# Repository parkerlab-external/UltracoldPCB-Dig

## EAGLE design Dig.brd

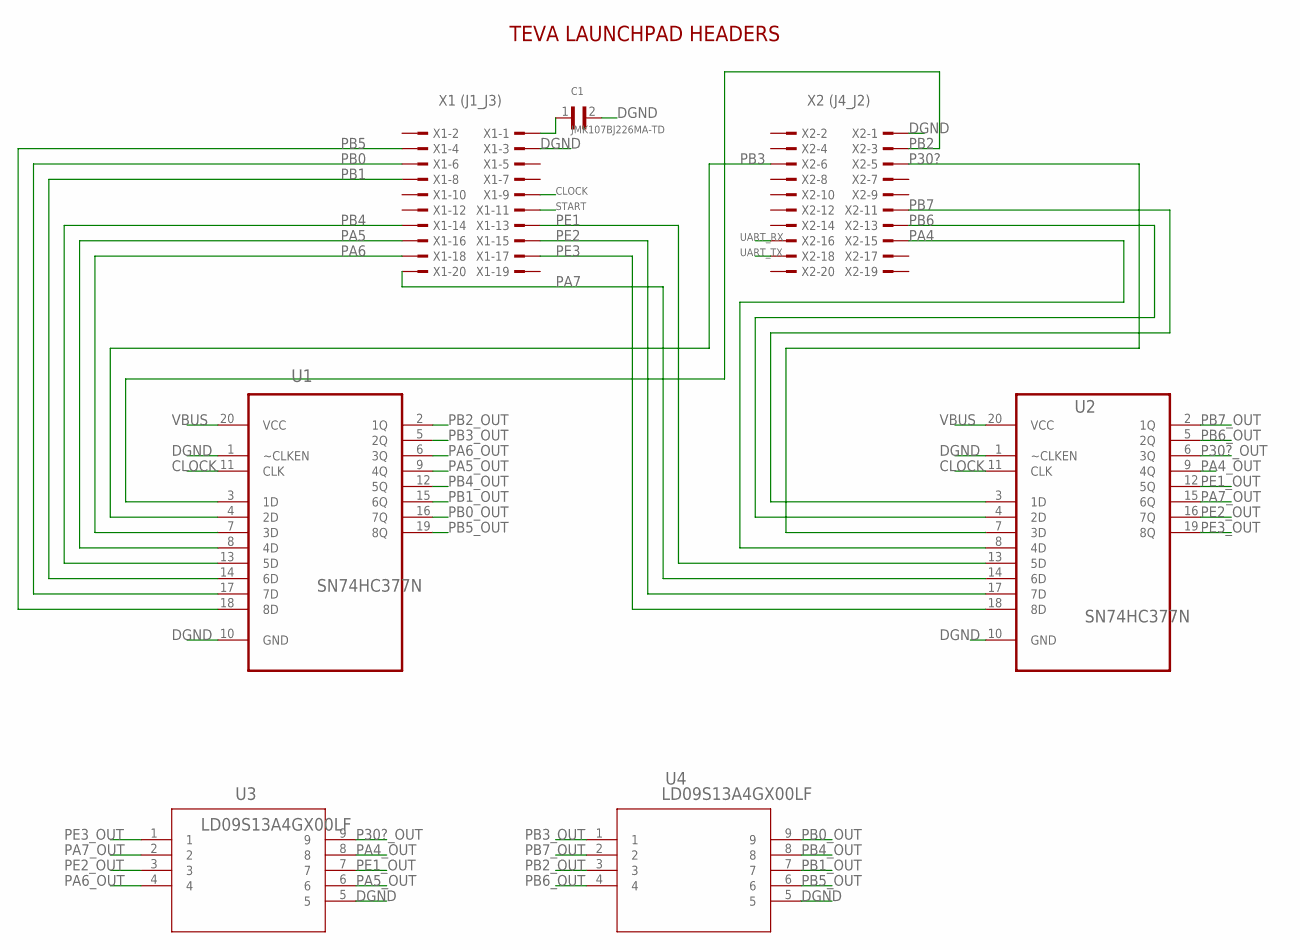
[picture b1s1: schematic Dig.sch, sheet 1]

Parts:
C1: JMK107BJ226MA-TD; CAPC1608X90N
U1, U2: SN74HC377N; DIP254P762X508-20
U3, U4: LD09S13A4GX00LF; LD09S13A4GX00LF_AMP
X1: X1 (J1_J3); TSW-110-XX-G-D
X2: X2 (J4_J2); TSW-110-XX-G-D

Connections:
CLOCK: U1.11 (CLK), U2.11 (CLK), X1.9
DGND: C1.2, U1.1 (~CLKEN), U1.10 (GND), U2.1 (~CLKEN), U2.10 (GND), U3.5, U4.5, X1.3, X2.1
P30?: U2.7 (3D), X2.5
P30?_OUT: U2.6 (3Q), U3.9
PA4: U2.8 (4D), X2.15
PA4_OUT: U2.9 (4Q), U3.8
PA5: U1.8 (4D), X1.16
PA5_OUT: U1.9 (4Q), U3.6
PA6: U1.7 (3D), X1.18
PA6_OUT: U1.6 (3Q), U3.4
PA7: U2.14 (6D), X1.20
PA7_OUT: U2.15 (6Q), U3.2
PB0: U1.17 (7D), X1.6
PB0_OUT: U1.16 (7Q), U4.9
PB1: U1.14 (6D), X1.8
PB1_OUT: U1.15 (6Q), U4.7
PB2: U1.3 (1D), X2.3
PB2_OUT: U1.2 (1Q), U4.3
PB3: U1.4 (2D), X2.6
PB3_OUT: U1.5 (2Q), U4.1
PB4: U1.13 (5D), X1.14
PB4_OUT: U1.12 (5Q), U4.8
PB5: U1.18 (8D), X1.4
PB5_OUT: U1.19 (8Q), U4.6
PB6: U2.4 (2D), X2.13
PB6_OUT: U2.5 (2Q), U4.4
PB7: U2.3 (1D), X2.11
PB7_OUT: U2.2 (1Q), U4.2
PE1: U2.13 (5D), X1.13
PE1_OUT: U2.12 (5Q), U3.7
PE2: U2.17 (7D), X1.15
PE2_OUT: U2.16 (7Q), U3.3
PE3: U2.18 (8D), X1.17
PE3_OUT: U2.19 (8Q), U3.1
START: X1.11
UART_RX: X2.16
UART_TX: X2.18
VBUS: C1.1, U1.20 (VCC), U2.20 (VCC), X1.1

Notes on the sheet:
TEVA LAUNCHPAD HEADERS

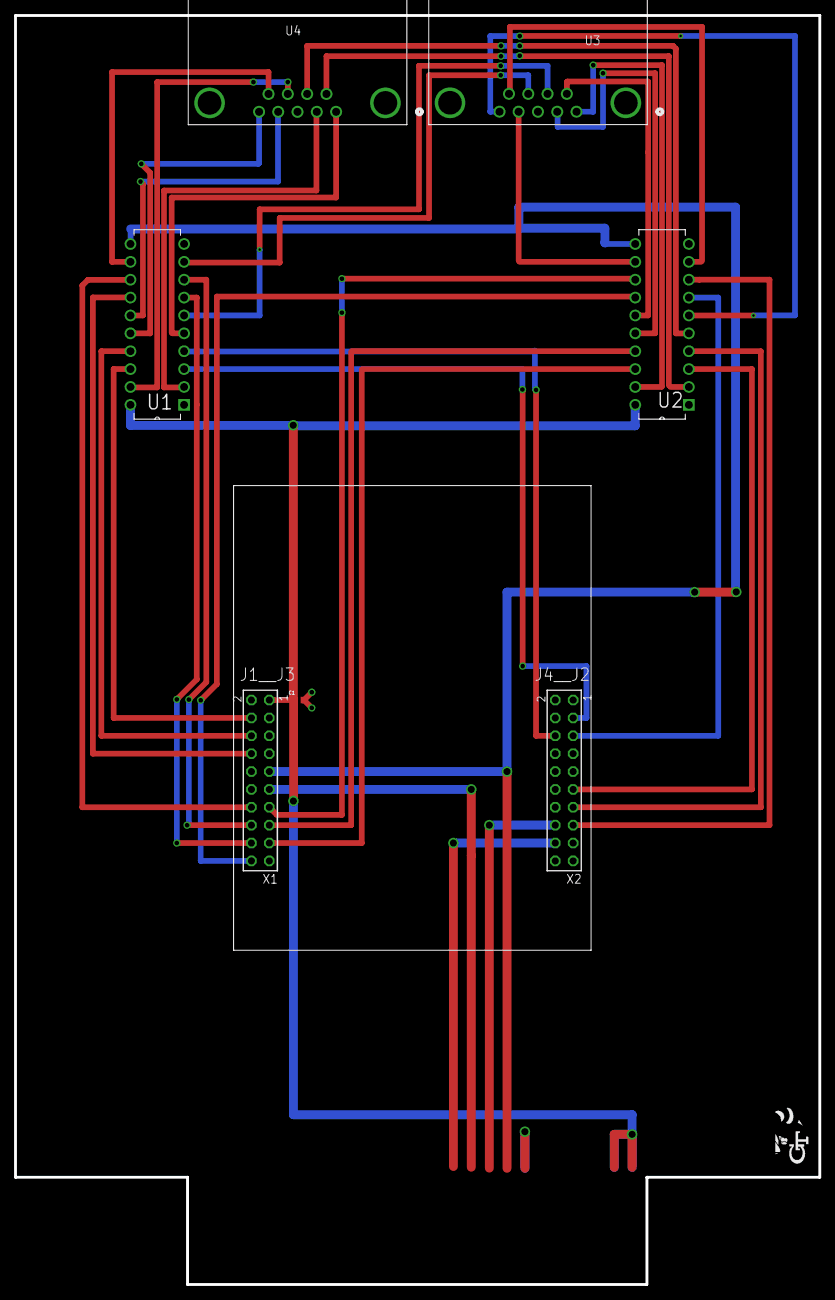
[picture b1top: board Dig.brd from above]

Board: 4 copper layers, 114.3 x 180.3 mm, 7 parts (0 on the bottom side), 35 nets.

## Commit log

2025-03-03 Design files.

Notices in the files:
parts and their libraries:
COPYRIGHT: Copyright (C) 2018 Accelerated Designs. All rights reserved
